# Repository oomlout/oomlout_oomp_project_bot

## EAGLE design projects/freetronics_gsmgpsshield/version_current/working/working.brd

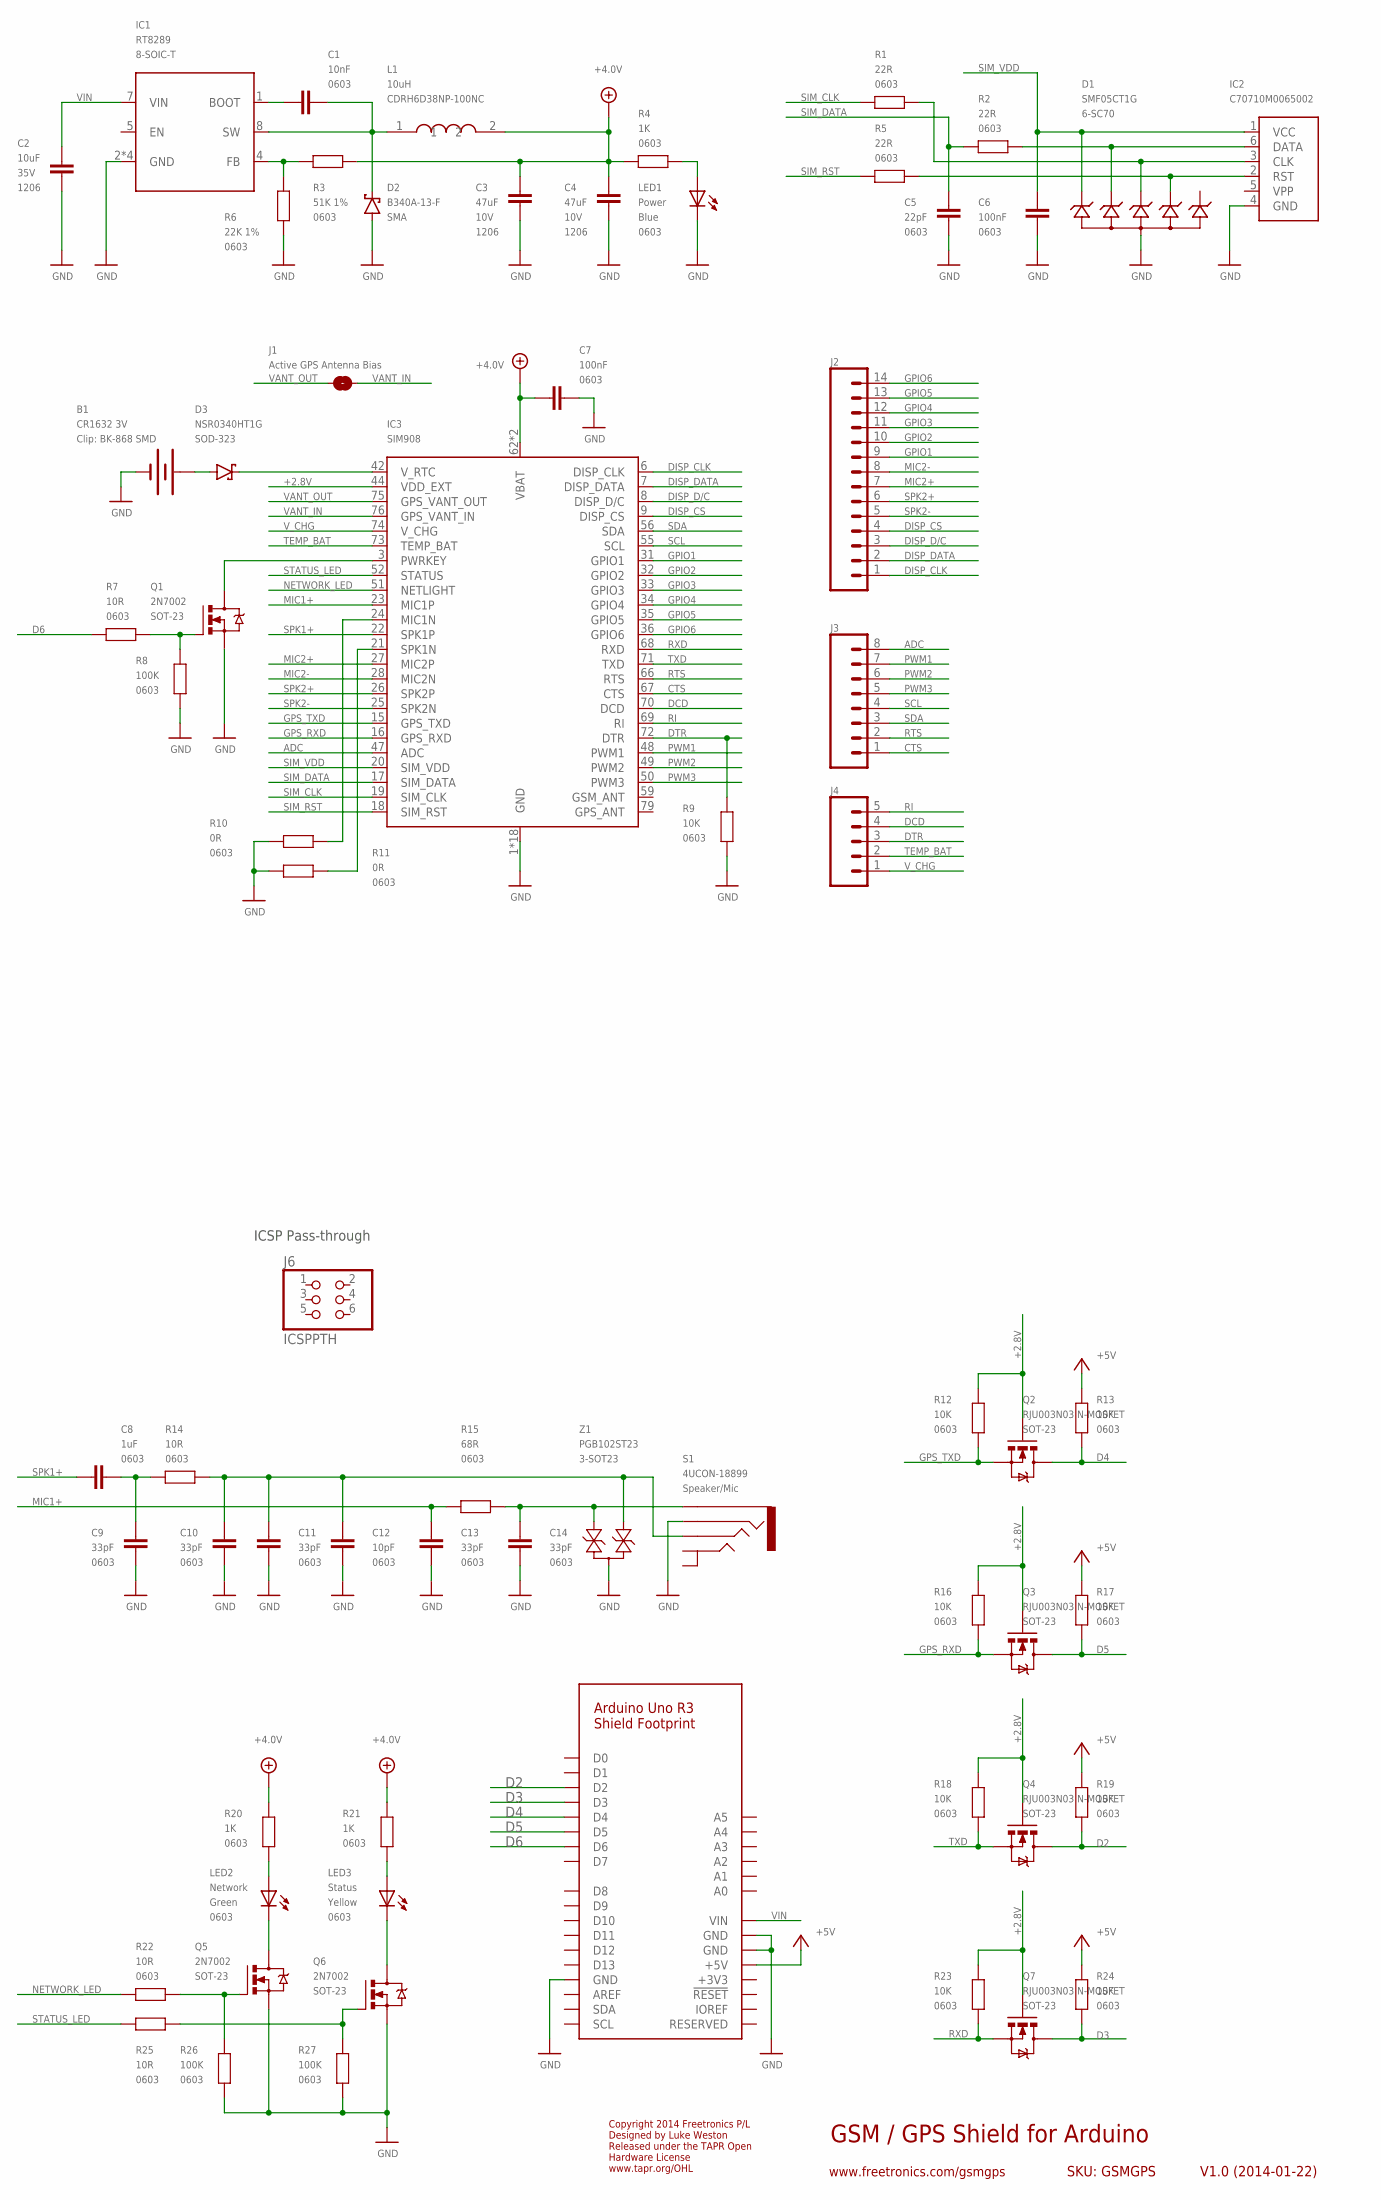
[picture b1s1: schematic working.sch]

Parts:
B1: CR1632 3V; BATCON_16MM
C1: 10nF; 0603
C2: 10uF; C1206; VOLTAGE 35V
C3, C4: 47uF; C1206; VOLTAGE 10V
C5: 22pF; 0603
C6, C7: 100nF; 0603
C8: 1uF; 0603
C9, C10, C11, C13, C14: 33pF; 0603
C12: 10pF; 0603
D1: SMF05CT1G; SC70-6
D2: B340A-13-F; SMA
D3: NSR0340HT1G; SOD-323
IC1: RT8289; SO08T
IC2: C70710M0065002
IC3: SIM908
J1: Active GPS Antenna Bias; SJ
J2: M14; 1X14
J3: M08STD; 1X08
J4: M05PTH; 1X05
J5: ARDUINO-SHIELD_R3_NOISP
J6: ICSPPTH; 2X03PTH
L1: 10uH; CDRH
LED1: Power; LED-0603
LED2: Network; LED-0603
LED3: Status; LED-0603
Q1, Q5, Q6: 2N7002; SOT23-3
Q2, Q3, Q4, Q7: RJU003N03 N-MOSFET; SOT32-3
R1, R2, R5: 22R; 0603
R3: 51K 1%; 0603
R4, R20, R21: 1K; 0603
R6: 22K 1%; 0603
R7, R14, R22, R25: 10R; 0603
R8, R26, R27: 100K; 0603
R9, R12, R13, R16, R17, R18, R19, R23, R24: 10K; 0603
R10, R11: 0R; 0603
R15: 68R; 0603
S1: 4UCON-18899
Z1: PGB102ST23; SOT23-3

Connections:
+2.8V: IC3.44 (VDD_EXT), Q2.1 (G), Q3.1 (G), Q4.1 (G), Q7.1 (G), R12.1, R16.1, R18.1, R23.1
+3V3: J5.3V3 (+3V3)
+4.0V: C3.1, C4.1, C7.2, IC3.62 (VBAT), IC3.63 (VBAT), L1.2, R3.1, R4.1, R20.1, R21.1
+5V: J5.+5V, R13.1, R17.1, R19.1, R24.1
ADC: IC3.47 (ADC), J3.8
CTS: IC3.67 (CTS), J3.1
D2: J5.D2, Q4.3 (D), R19.2
D3: J5.D3, Q7.3 (D), R24.2
D4: J5.D4, Q2.3 (D), R13.2
D5: J5.D5, Q3.3 (D), R17.2
D6: J5.D6, R7.2
DCD: IC3.70 (DCD), J4.4
DISP_CLK: IC3.6 (DISP_CLK), J2.1
DISP_CS: IC3.9 (DISP_CS), J2.4
DISP_D/C: IC3.8 (DISP_D/C), J2.3
DISP_DATA: IC3.7 (DISP_DATA), J2.2
DTR: IC3.72 (DTR), J4.3, R9.1
GND: B1.GND (-), C2.2, C3.2, C4.2, C5.1, C6.1, C7.1, C9.1, C10.1, C11.1, C12.1, C13.1, C14.1, D1.2 (A2), D2.A, IC1.2 (GND), IC1.3 (GND), IC1.6 (GND), IC1.PAD (GND), IC2.4 (GND), IC3.1 (GND), IC3.2 (GND), IC3.5 (GND), IC3.10 (GND), IC3.14 (GND), IC3.37 (GND), IC3.40 (GND), IC3.41 (GND), IC3.43 (GND), IC3.57 (GND), IC3.58 (GND), IC3.60 (GND), IC3.61 (GND), IC3.64 (GND), IC3.65 (GND), IC3.77 (GND), IC3.78 (GND), IC3.80 (GND), J5.GND, J5.GND@0 (GND), J5.GND@1 (GND), LED1.C, Q1.2 (S), Q5.2 (S), Q6.2 (S), R6.1, R8.1, R9.2, R10.2, R11.2, R26.1, R27.1, S1.4, Z1.3
GPIO1: IC3.31 (GPIO1), J2.9
GPIO2: IC3.32 (GPIO2), J2.10
GPIO3: IC3.33 (GPIO3), J2.11
GPIO4: IC3.34 (GPIO4), J2.12
GPIO5: IC3.35 (GPIO5), J2.13
GPIO6: IC3.36 (GPIO6), J2.14
GPS_RXD: IC3.16 (GPS_RXD), Q3.2 (S), R16.2
GPS_TXD: IC3.15 (GPS_TXD), Q2.2 (S), R12.2
MIC1+: C13.2, IC3.23 (MIC1P), R15.1
MIC2+: IC3.27 (MIC2P), J2.7
MIC2-: IC3.28 (MIC2N), J2.8
unnamed: LED1.A, R4.2
unnamed: LED2.C, Q5.3 (D)
unnamed: LED3.C, Q6.3 (D)
unnamed: Q5.1 (G), R22.1, R26.2
unnamed: Q6.1 (G), R25.1, R27.2
unnamed: D3.K, IC3.42 (V_RTC)
unnamed: IC3.3 (PWRKEY), Q1.3 (D)
unnamed: B1.PWR@1 (+), D3.A
unnamed: IC3.21 (SPK1N), R11.1
unnamed: IC3.24 (MIC1N), R10.1
unnamed: D1.5 (K5), IC2.2 (RST), R5.1
unnamed: D1.4 (K4), IC2.3 (CLK), R1.1
unnamed: D1.3 (K3), IC2.6 (DATA), R2.1
unnamed: C14.2, R15.2, S1.1, Z1.2
unnamed: C10.2, C11.2, C12.2, R14.2, S1.3, Z1.1
unnamed: C8.1, C9.2, R14.1
unnamed: Q1.1 (G), R7.1, R8.2
unnamed: LED3.A, R21.2
unnamed: LED2.A, R20.2
unnamed: C1.1, D2.K, IC1.8 (SW), L1.1
unnamed: IC1.4 (FB), R3.2, R6.2
unnamed: C1.2, IC1.1 (BOOT)
NETWORK_LED: IC3.51 (NETLIGHT), R22.2
PWM1: IC3.48 (PWM1), J3.7
PWM2: IC3.49 (PWM2), J3.6
PWM3: IC3.50 (PWM3), J3.5
RI: IC3.69 (RI), J4.5
RTS: IC3.66 (RTS), J3.2
RXD: IC3.68 (RXD), Q7.2 (S), R23.2
SCL: IC3.55 (SCL), J3.4
SDA: IC3.56 (SDA), J3.3
SIM_CLK: IC3.19 (SIM_CLK), R1.2
SIM_DATA: C5.2, IC3.17 (SIM_DATA), R2.2
SIM_RST: IC3.18 (SIM_RST), R5.2
SIM_VDD: C6.2, D1.1 (K1), IC2.1 (VCC), IC3.20 (SIM_VDD)
SPK1+: C8.2, IC3.22 (SPK1P)
SPK2+: IC3.26 (SPK2P), J2.6
SPK2-: IC3.25 (SPK2N), J2.5
STATUS_LED: IC3.52 (STATUS), R25.2
TEMP_BAT: IC3.73 (TEMP_BAT), J4.2
TXD: IC3.71 (TXD), Q4.2 (S), R18.2
VANT_IN: IC3.76 (GPS_VANT_IN), J1.2
VANT_OUT: IC3.75 (GPS_VANT_OUT), J1.1
VIN: C2.1, IC1.7 (VIN), J5.VIN
V_CHG: IC3.74 (V_CHG), J4.1

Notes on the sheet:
GSM / GPS Shield for Arduino
V1.0 (2014-01-22)
www.freetronics.com/gsmgps
SKU: GSMGPS
Copyright 2014 Freetronics P/L Designed by Luke Weston Released under the TAPR Open Hardware License www.tapr.org/OHL
ICSP Pass-through

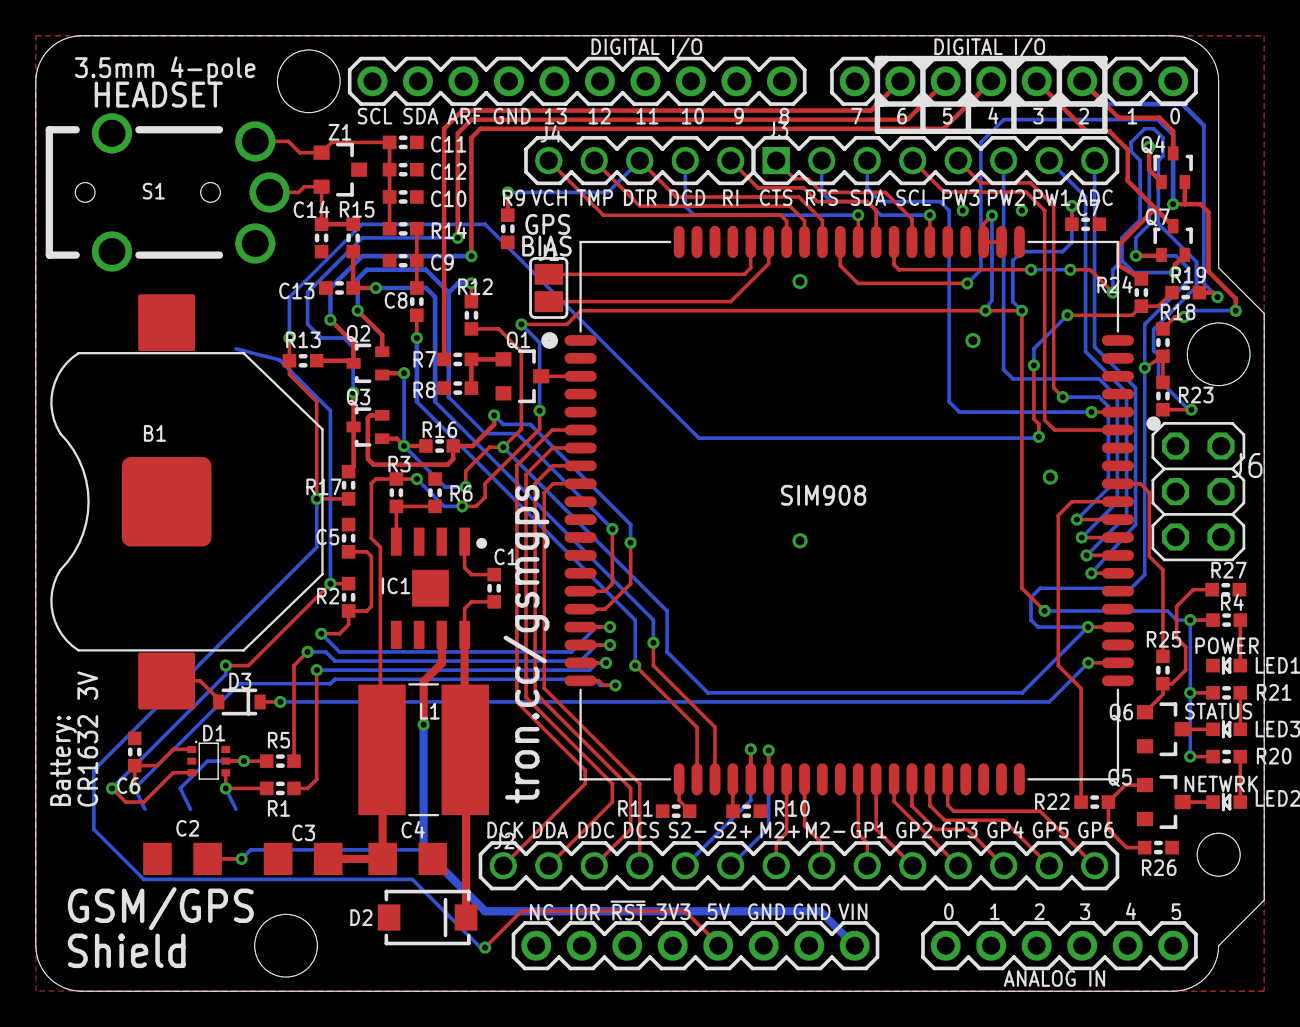
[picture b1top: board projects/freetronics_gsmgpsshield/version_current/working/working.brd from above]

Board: 2 copper layers, 68.6 x 53.3 mm, 67 parts (1 on the bottom side), 73 nets.

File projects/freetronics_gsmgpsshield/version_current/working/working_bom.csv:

"Id";"Designator";"Footprint";"Quantity";"Designation";"Supplier and ref";
1;"C14,C10,C9,C13,C11";"0603";5;"33pF";;;
2;"R1,R2,R5";"0603";3;"22R";;;
3;"R14,R25,R7,R22";"0603";4;"10R";;;
4;"C4,C3";"C1206";2;"47uF";;;
5;"Q2,Q4,Q3,Q7";"SOT32-3";4;"RJU003N03 N-MOSFET";;;
6;"C6,C7";"0603";2;"100nF";;;
7;"R15";"0603";1;"68R";;;
8;"R27,R26,R8";"0603";3;"100K";;;
9;"R20,R21,R4";"0603";3;"1K";;;
10;"Q1,Q5,Q6";"SOT23-3";3;"2N7002";;;
11;"R9,R18,R24,R19,R12,R13,R23,R16,R17";"0603";9;"10K";;;
12;"D2";"SMA";1;"B340A-13-F";;;
13;"R11,R10";"0603";2;"0R";;;
14;"C5";"0603";1;"22pF";;;
15;"R3";"0603";1;"51K 1%";;;
16;"L1";"CDRH";1;"10uH";;;
17;"LED3";"LED-0603";1;"Status";;;
18;"J3";"1X08";1;"";;;
19;"R6";"0603";1;"22K 1%";;;
20;"C8";"0603";1;"1uF";;;
21;"J1";"SJ";1;"Active GPS Antenna Bias";;;
22;"D1";"SC70-6";1;"SMF05CT1G";;;
23;"LED1";"LED-0603";1;"Power";;;
24;"IC3";"SIM908";1;"SIM908";;;
25;"J2";"1X14";1;"";;;
26;"LED2";"LED-0603";1;"Network";;;
27;"IC1";"SO08T";1;"RT8289";;;
28;"D3";"SOD-323";1;"NSR0340HT1G";;;
29;"J4";"1X05";1;"";;;
30;"B1";"BATCON_16MM";1;"CR1632 3V";;;
31;"S1";"4UCON-18899";1;"4UCON-18899";;;
32;"J6";"2X03PTH";1;"ICSPPTH";;;
33;"C12";"0603";1;"10pF";;;
34;"C2";"C1206";1;"10uF";;;
35;"Z1";"SOT23-3";1;"PGB102ST23";;;
36;"C1";"0603";1;"10nF";;;
37;"J5";"ARDUINO-SHIELD_R3_NOISP";1;"ARDUINO-SHIELD_R3_NOISP";;;
38;"IC2";"C70710M0065002";1;"C70710M0065002";;;

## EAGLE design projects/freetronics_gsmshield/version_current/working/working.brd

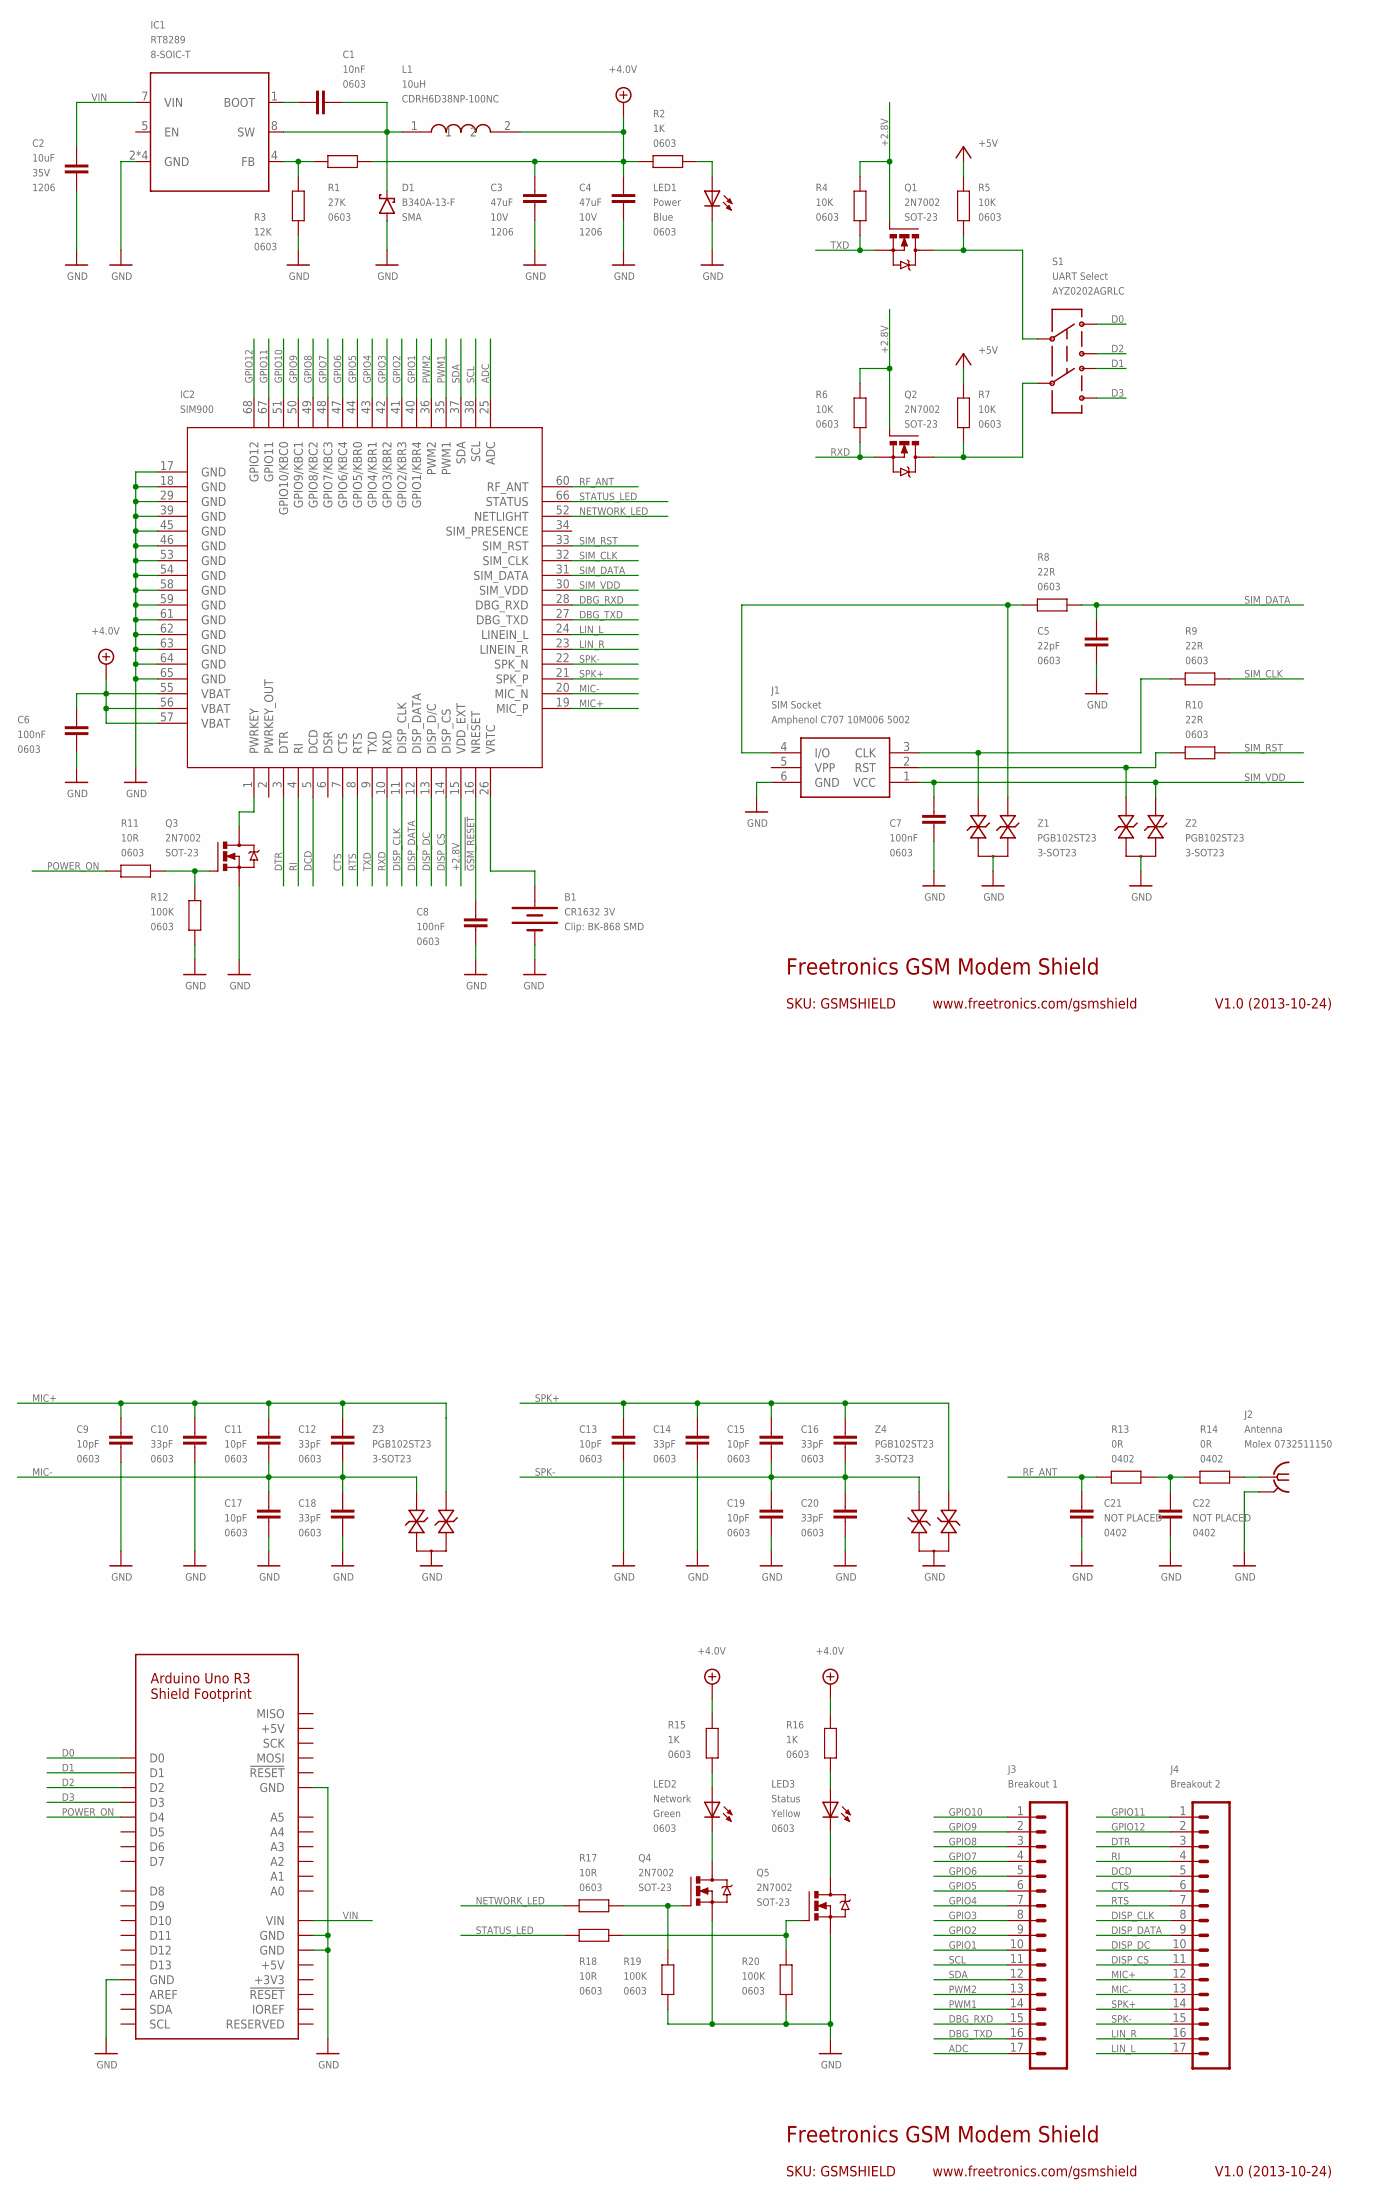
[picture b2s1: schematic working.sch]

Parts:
B1: CR1632 3V; BATCON_16MM
C1: 10nF; 0603
C2: 10uF; C1206; VOLTAGE 35V
C3, C4: 47uF; C1206; VOLTAGE 10V
C5: 22pF; 0603
C6, C7, C8: 100nF; 0603
C9, C11, C13, C15, C17, C19: 10pF; 0603
C10, C12, C14, C16, C18, C20: 33pF; 0603
C21, C22: NOT PLACED; C0402
D1: B340A-13-F; SMA
IC1: RT8289; SO08T
IC2: SIM900
J1: SIM Socket; SIMHOLDER3
J2: Antenna; J502-ND-142-0701-881/886
J3: Breakout 1; 1X17
J4: Breakout 2; 1X17
J5: ARDUINO-SHIELD_R3
L1: 10uH; CDRH
LED1: Power; LED-0603
LED2: Network; LED-0603
LED3: Status; LED-0603
Q1, Q2, Q3, Q4, Q5: 2N7002; SOT23-3
R1: 27K; 0603
R2, R15, R16: 1K; 0603
R3: 12K; 0603
R4, R5, R6, R7: 10K; 0603
R8, R9, R10: 22R; 0603
R11, R17, R18: 10R; 0603
R12, R19, R20: 100K; 0603
R13, R14: 0R; C0402
S1: UART Select; AYZ0202
Z1, Z2, Z3, Z4: PGB102ST23; SOT23-3

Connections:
!GSM_RESET: C8.2, IC2.16 (NRESET)
+2.8V: IC2.15 (VDD_EXT), Q1.1 (G), Q2.1 (G), R4.1, R6.1
+3V3: J5.3V3 (+3V3)
+4.0V: C3.1, C4.1, C6.2, IC2.55 (VBAT), IC2.56 (VBAT), IC2.57 (VBAT), L1.2, R1.1, R2.1, R15.1, R16.1
+5V: J5.+5V, R5.1, R7.1
ADC: IC2.25 (ADC), J3.17
CTS: IC2.7 (CTS), J4.6
D0: J5.D0, S1.1
D1: J5.D1, S1.4
D2: J5.D2, S1.3
D3: J5.D3, S1.6
DBG_RXD: IC2.28 (DBG_RXD), J3.15
DBG_TXD: IC2.27 (DBG_TXD), J3.16
DCD: IC2.5 (DCD), J4.5
DISP_CLK: IC2.11 (DISP_CLK), J4.8
DISP_CS: IC2.14 (DISP_CS), J4.11
DISP_DATA: IC2.12 (DISP_DATA), J4.9
DISP_DC: IC2.13 (DISP_D/C), J4.10
DTR: IC2.3 (DTR), J4.3
GND: B1.GND (-), C2.2, C3.2, C4.2, C5.1, C6.1, C7.1, C8.1, C9.1, C10.1, C13.1, C14.1, C17.1, C18.1, C19.1, C20.1, C21.1, C22.1, D1.A, IC1.2 (GND), IC1.3 (GND), IC1.6 (GND), IC1.PAD (GND), IC2.17 (GND), IC2.18 (GND), IC2.29 (GND), IC2.39 (GND), IC2.45 (GND), IC2.46 (GND), IC2.53 (GND), IC2.54 (GND), IC2.58 (GND), IC2.59 (GND), IC2.61 (GND), IC2.62 (GND), IC2.63 (GND), IC2.64 (GND), IC2.65 (GND), J1.6 (GND), J2.G@1 (GND), J2.G@2 (GND), J2.G@3 (GND), J2.G@4 (GND), J5.GND, J5.GND@0 (GND), J5.GND@1 (GND), J5.GND@2 (GND), LED1.C, Q3.2 (S), Q4.2 (S), Q5.2 (S), R3.1, R12.1, R19.1, R20.1, Z1.3, Z2.3, Z3.3, Z4.3
GPIO1: IC2.40 (GPIO1/KBR4), J3.10
GPIO2: IC2.41 (GPIO2/KBR3), J3.9
GPIO3: IC2.42 (GPIO3/KBR2), J3.8
GPIO4: IC2.43 (GPIO4/KBR1), J3.7
GPIO5: IC2.44 (GPIO5/KBR0), J3.6
GPIO6: IC2.47 (GPIO6/KBC4), J3.5
GPIO7: IC2.48 (GPIO7/KBC3), J3.4
GPIO8: IC2.49 (GPIO8/KBC2), J3.3
GPIO9: IC2.50 (GPIO9/KBC1), J3.2
GPIO10: IC2.51 (GPIO10/KBC0), J3.1
GPIO11: IC2.67 (GPIO11), J4.1
GPIO12: IC2.68 (GPIO12), J4.2
LIN_L: IC2.24 (LINEIN_L), J4.17
LIN_R: IC2.23 (LINEIN_R), J4.16
MIC+: C9.2, C10.2, C11.2, C12.2, IC2.19 (MIC_P), J4.12, Z3.2
MIC-: C11.1, C12.1, C17.2, C18.2, IC2.20 (MIC_N), J4.13, Z3.1
unnamed: LED1.A, R2.2
unnamed: LED2.C, Q4.3 (D)
unnamed: LED3.C, Q5.3 (D)
unnamed: Q4.1 (G), R17.1, R19.2
unnamed: Q5.1 (G), R18.1, R20.2
unnamed: B1.PWR@1 (+), IC2.26 (VRTC)
unnamed: J1.2 (RST), R10.2, Z2.1
unnamed: J1.3 (CLK), R9.2, Z1.1
unnamed: J1.4 (I/O), R8.2, Z1.2
unnamed: IC2.1 (PWRKEY), Q3.3 (D)
unnamed: Q3.1 (G), R11.1, R12.2
unnamed: C22.2, R13.2, R14.1
unnamed: J2.1, R14.2
unnamed: LED3.A, R16.2
unnamed: LED2.A, R15.2
unnamed: C1.1, D1.K, IC1.8 (SW), L1.1
unnamed: IC1.4 (FB), R1.2, R3.2
unnamed: C1.2, IC1.1 (BOOT)
NETWORK_LED: IC2.52 (NETLIGHT), R17.2
POWER_ON: J5.D4, R11.2
PWM1: IC2.35 (PWM1), J3.14
PWM2: IC2.36 (PWM2), J3.13
RF_ANT: C21.2, IC2.60 (RF_ANT), R13.1
RI: IC2.4 (RI), J4.4
RTS: IC2.8 (RTS), J4.7
RXD: IC2.10 (RXD), Q2.2 (S), R6.2
RXD_5V: Q2.3 (D), R7.2, S1.5
SCL: IC2.38 (SCL), J3.11
SDA: IC2.37 (SDA), J3.12
SIM_CLK: IC2.32 (SIM_CLK), R9.1
SIM_DATA: C5.2, IC2.31 (SIM_DATA), R8.1
SIM_RST: IC2.33 (SIM_RST), R10.1
SIM_VDD: C7.2, IC2.30 (SIM_VDD), J1.1 (VCC), Z2.2
SPK+: C13.2, C14.2, C15.2, C16.2, IC2.21 (SPK_P), J4.14, Z4.1
SPK-: C15.1, C16.1, C19.2, C20.2, IC2.22 (SPK_N), J4.15, Z4.2
STATUS_LED: IC2.66 (STATUS), R18.2
TXD: IC2.9 (TXD), Q1.2 (S), R4.2
TXD_5V: Q1.3 (D), R5.2, S1.2
VIN: C2.1, IC1.7 (VIN), J5.VIN

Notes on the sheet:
Freetronics GSM Modem Shield
V1.0 (2013-10-24)
www.freetronics.com/gsmshield
SKU: GSMSHIELD

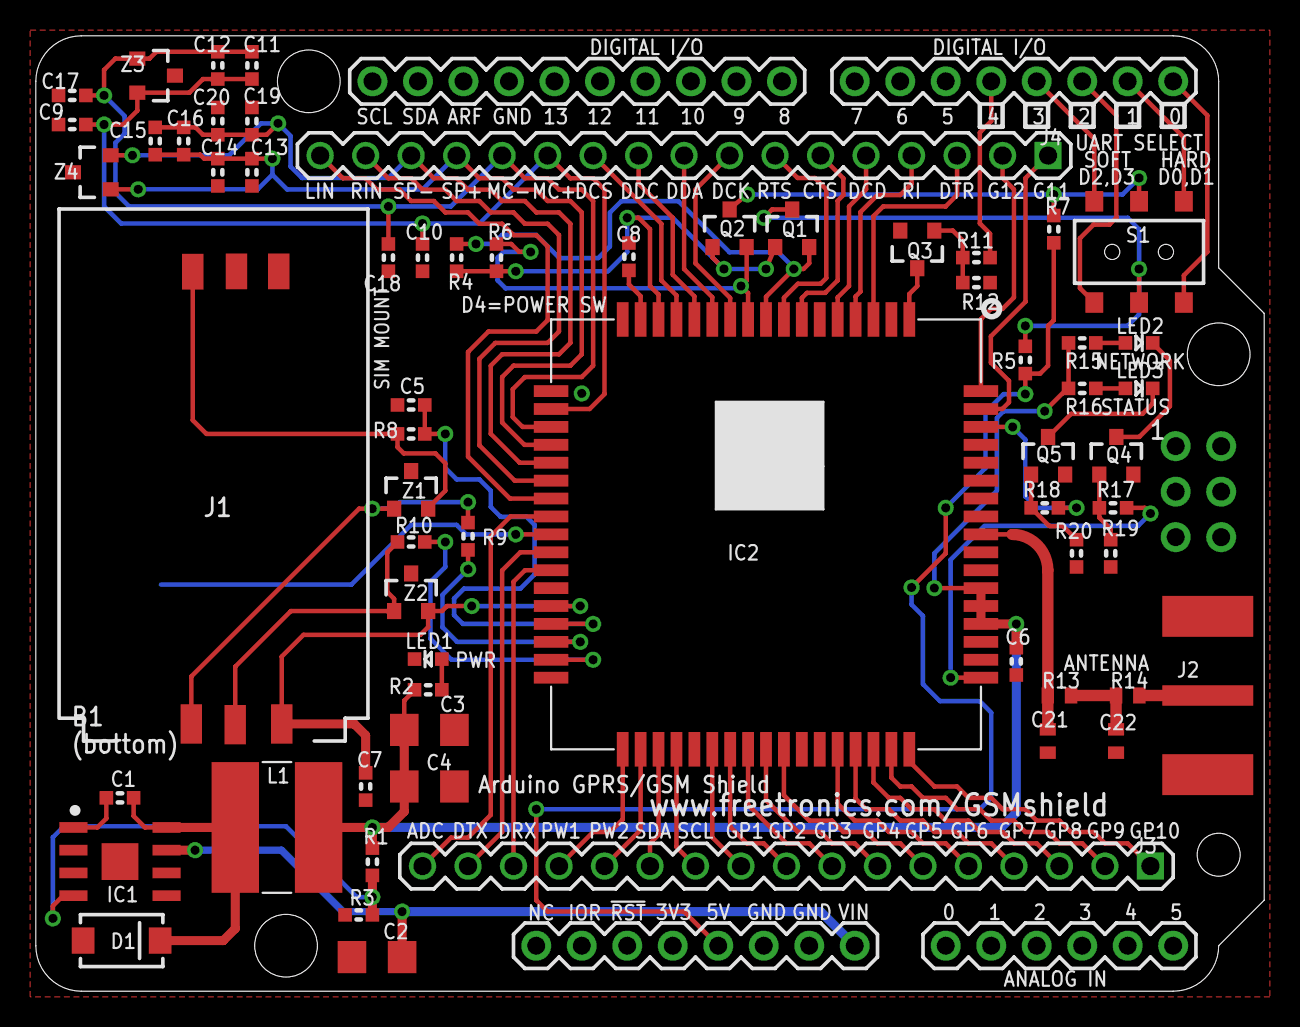
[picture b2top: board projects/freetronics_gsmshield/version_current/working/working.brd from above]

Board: 2 copper layers, 68.6 x 53.3 mm, 65 parts (1 on the bottom side), 74 nets.

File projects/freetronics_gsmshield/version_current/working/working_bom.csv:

"Id";"Designator";"Footprint";"Quantity";"Designation";"Supplier and ref";
1;"R6,R7,R5,R4";"0603";4;"10K";;;
2;"R15,R2,R16";"0603";3;"1K";;;
3;"C1";"0603";1;"10nF";;;
4;"C10,C14,C16,C18,C12,C20";"0603";6;"33pF";;;
5;"J4";"1X17";1;"Breakout 2";;;
6;"R10,R8,R9";"0603";3;"22R";;;
7;"LED2";"LED-0603";1;"Network";;;
8;"J3";"1X17";1;"Breakout 1";;;
9;"R14,R13";"C0402";2;"0R";;;
10;"S1";"AYZ0202";1;"UART Select";;;
11;"J2";"J502-ND-142-0701-881_886";1;"Antenna";;;
12;"Q1,Q5,Q2,Q4,Q3";"SOT23-3";5;"2N7002";;;
13;"C13,C17,C9,C19,C15,C11";"0603";6;"10pF";;;
14;"Z4,Z2,Z3,Z1";"SOT23-3";4;"PGB102ST23";;;
15;"R20,R19,R12";"0603";3;"100K";;;
16;"C7,C8,C6";"0603";3;"100nF";;;
17;"C22,C21";"C0402";2;"NOT PLACED";;;
18;"L1";"CDRH";1;"10uH";;;
19;"C3,C4";"C1206";2;"47uF";;;
20;"R11,R17,R18";"0603";3;"10R";;;
21;"LED3";"LED-0603";1;"Status";;;
22;"LED1";"LED-0603";1;"Power";;;
23;"IC1";"SO08T";1;"RT8289";;;
24;"C5";"0603";1;"22pF";;;
25;"C2";"C1206";1;"10uF";;;
26;"D1";"SMA";1;"B340A-13-F";;;
27;"J5";"ARDUINO-SHIELD_R3";1;"ARDUINO-SHIELD_R3";;;
28;"R3";"0603";1;"12K";;;
29;"R1";"0603";1;"27K";;;
30;"IC2";"SIM900";1;"SIM900";;;
31;"J1";"SIMHOLDER3";1;"SIM Socket";;;
32;"B1";"BATCON_16MM";1;"CR1632 3V";;;

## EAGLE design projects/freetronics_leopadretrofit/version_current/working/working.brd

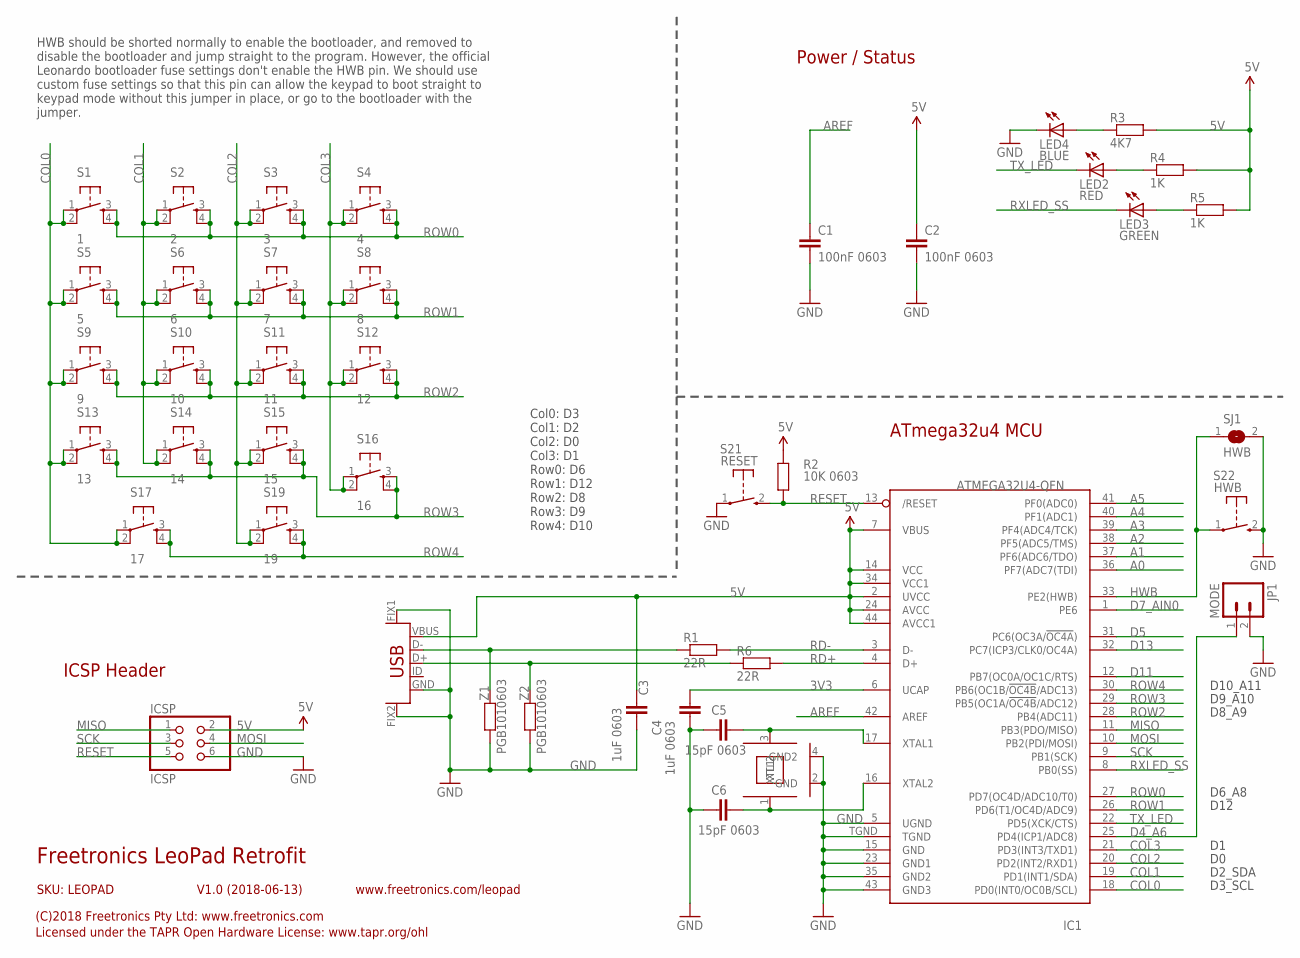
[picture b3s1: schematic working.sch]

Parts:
C1, C2: 100nF 0603; 0603
C3, C4: 1uF 0603; 0603
C5, C6: 15pF 0603; 0603
IC1: ATMEGA32U4-QFN; QFN-44N
ICSP: ICSP; 2X03
JP1: MODE; 1X02
LED2: RED; LED-0603
LED3: GREEN; LED-0603
LED4: BLUE; LED3MM
R1, R6: 22R; 0603
R2: 10K 0603; 0603
R3: 4K7; 0603
R4, R5: 1K; 0603
S1: 1; TACTILE_SWITCH_SMD
S2: 2; TACTILE_SWITCH_SMD
S3: 3; TACTILE_SWITCH_SMD
S4: 4; TACTILE_SWITCH_SMD
S5: 5; TACTILE_SWITCH_SMD
S6: 6; TACTILE_SWITCH_SMD
S7: 7; TACTILE_SWITCH_SMD
S8: 8; TACTILE_SWITCH_SMD
S9: 9; TACTILE_SWITCH_SMD
S10: 10; TACTILE_SWITCH_SMD
S11: 11; TACTILE_SWITCH_SMD
S12: 12; TACTILE_SWITCH_SMD
S13: 13; TACTILE_SWITCH_SMD
S14: 14; TACTILE_SWITCH_SMD
S15: 15; TACTILE_SWITCH_SMD
S16: 16; TACTILE_SWITCH_SMD
S17: 17; TACTILE_SWITCH_SMD
S19: 19; TACTILE_SWITCH_SMD
S21: RESET; TACTILE_SWITCH_SMD_2PIN_TINY
S22: HWB; TACTILE_SWITCH_SMD_2PIN_TINY
SJ1: HWB; SJ
U$2: USB-2P2P; USB-MICROB-MB05PMXX
XTL1: 16MHz; CRYSTAL-SMD-3X2
Z1, Z2: PGB1010603; 0603

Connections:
3V3: C4.2, IC1.6 (UCAP)
5V: C2.1, C3.1, IC1.2 (UVCC), IC1.7 (VBUS), IC1.14 (VCC), IC1.24 (AVCC), IC1.34 (VCC1), IC1.44 (AVCC1), ICSP.2, R2.2, R3.2, R4.2, R5.2, U$2.VBUS
A0: IC1.36 (PF7(ADC7(TDI))
A1: IC1.37 (PF6(ADC6/TDO))
A2: IC1.38 (PF5(ADC5/TMS))
A3: IC1.39 (PF4(ADC4/TCK))
A4: IC1.40 (PF1(ADC1))
A5: IC1.41 (PF0(ADC0))
AREF: C1.1, IC1.42 (AREF)
COL0: IC1.18 (PD0(INT0/OC0B/SCL)), S1.1, S1.2, S5.1, S5.2, S9.1, S9.2, S13.1, S13.2, S17.1, S17.2
COL1: IC1.19 (PD1(INT1/SDA)), S2.1, S2.2, S6.1, S6.2, S10.1, S10.2, S14.1, S14.2
COL2: IC1.20 (PD2(INT2/RXD1)), S3.1, S3.2, S7.1, S7.2, S11.1, S11.2, S15.1, S15.2, S19.1, S19.2
COL3: IC1.21 (PD3(INT3/TXD1)), S4.1, S4.2, S8.1, S8.2, S12.1, S12.2, S16.1, S16.2
D4_A6: IC1.25 (PD4(ICP1/ADC8)), JP1.1
D5: IC1.31 (PC6(OC3A/!OC4A!))
D7_AIN0: IC1.1 (PE6)
D11: IC1.12 (PB7(OC0A/OC1C/RTS))
D13: IC1.32 (PC7(ICP3/CLK0/OC4A))
D+: R6.1, U$2.D+, Z2.2
D-: R1.1, U$2.D-, Z1.2
GND: C1.2, C2.2, C3.2, C4.1, C5.1, C6.1, IC1.5 (UGND), IC1.15 (GND), IC1.23 (GND1), IC1.35 (GND2), IC1.43 (GND3), IC1.TGND, ICSP.6, JP1.2, LED4.K (C), S21.1, S22.2 (S), SJ1.2, U$2.FIX1 (TAB1), U$2.FIX2 (TAB2), U$2.GND, XTL1.2 (GND), XTL1.4 (GND2), Z1.1, Z2.1
HWB: IC1.33 (PE2(HWB)), S22.1, SJ1.1
MISO: IC1.11 (PB3(PDO/MISO)), ICSP.1
MOSI: IC1.10 (PB2(PDI/MOSI)), ICSP.4
unnamed: LED4.A, R3.1
unnamed: LED2.A, R4.1
unnamed: LED3.A, R5.1
unnamed: C5.2, IC1.17 (XTAL1), XTL1.3 (XTL2)
unnamed: C6.2, IC1.16 (XTAL2), XTL1.1 (XTL1)
RD+: IC1.4 (D+), R6.2
RD-: IC1.3 (D-), R1.2
RESET: IC1.13 (/RESET), ICSP.5, R2.1, S21.2 (S)
ROW0: IC1.27 (PD7(OC4D/ADC10/T0)), S1.3, S1.4, S2.3, S2.4, S3.3, S3.4, S4.3, S4.4
ROW1: IC1.26 (PD6(T1/OC4D/ADC9)), S5.3, S5.4, S6.3, S6.4, S7.3, S7.4, S8.3, S8.4
ROW2: IC1.28 (PB4(ADC11)), S9.3, S9.4, S10.3, S10.4, S11.3, S11.4, S12.3, S12.4
ROW3: IC1.29 (PB5(OC1A/!OC4B!/ADC12)), S13.3, S13.4, S14.3, S14.4, S15.3, S15.4, S16.3, S16.4
ROW4: IC1.30 (PB6(OC1B/!OC4B!/ADC13)), S17.3, S17.4, S19.3, S19.4
RXLED_SS: IC1.8 (PB0(SS)), LED3.C
SCK: IC1.9 (PB1(SCK)), ICSP.3
TX_LED: IC1.22 (PD5(XCK/CTS)), LED2.C

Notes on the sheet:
ICSP Header
ATmega32u4 MCU
HWB should be shorted normally to enable the bootloader, and removed to disable the bootloader and jump straight to the program. However, the official Leonardo bootloader fuse settings don't enable the HWB pin. We should use custom fuse settings so that this pin can allow the keypad to boot straigh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
Freetronics LeoPad Retrofit
V1.0 (2018-06-13)
SKU: LEOPAD
(C)2018 Freetronics Pty Ltd: www.freetronics.com
Licensed under the TAPR Open Hardware License: www.tapr.org/ohl
www.freetronics.com/leopad
Power / Status
D2_SDA
D3_SCL
D10_A11
D9_A10
D8_A9
D6_A8
D12
Col0: D3 Col1: D2 Col2: D0 Col3: D1 Row0: D6 Row1: D12 Row2: D8 Row3: D9 Row4: D10

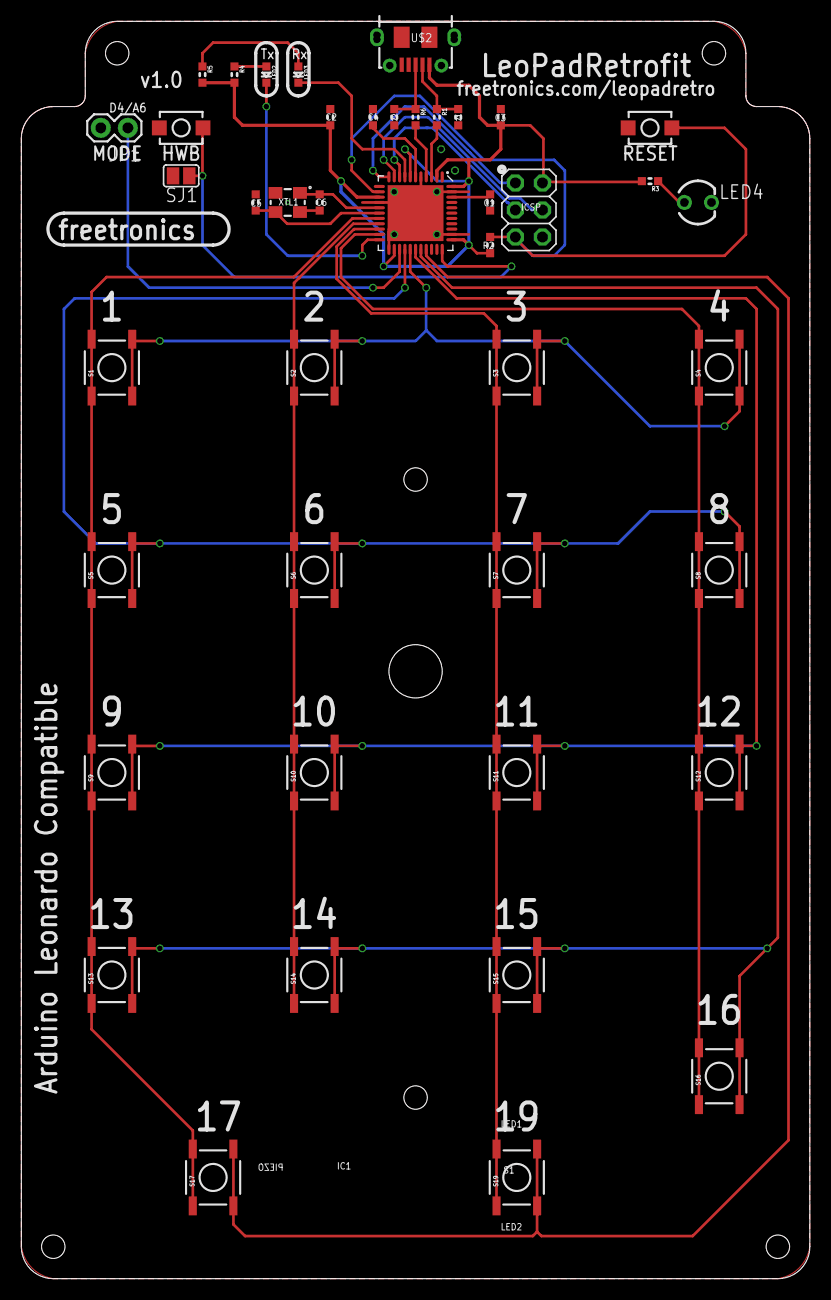
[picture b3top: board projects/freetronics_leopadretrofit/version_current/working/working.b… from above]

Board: 2 copper layers, 74.0 x 118.0 mm, 43 parts (0 on the bottom side), 30 nets.

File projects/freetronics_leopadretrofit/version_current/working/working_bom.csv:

"Id";"Designator";"Footprint";"Quantity";"Designation";"Supplier and ref";
1;"S17";"TACTILE_SWITCH_SMD";1;"17";;;
2;"@HOLE4,@HOLE3,@HOLE5,@HOLE1,@HOLE2,@HOLE0,@HOLE6";"";7;"";;;
3;"C4,C3";"0603";2;"1uF 0603";;;
4;"S21";"TACTILE_SWITCH_SMD_2PIN_TINY";1;"RESET";;;
5;"C5,C6";"0603";2;"15pF 0603";;;
6;"S12";"TACTILE_SWITCH_SMD";1;"12";;;
7;"S13";"TACTILE_SWITCH_SMD";1;"13";;;
8;"S9";"TACTILE_SWITCH_SMD";1;"9";;;
9;"C2,C1";"0603";2;"100nF 0603";;;
10;"S3";"TACTILE_SWITCH_SMD";1;"3";;;
11;"JP1";"1X02";1;"MODE";;;
12;"ICSP0";"2X03";1;"ICSP";;;
13;"S22";"TACTILE_SWITCH_SMD_2PIN_TINY";1;"HWB";;;
14;"Z1,Z2";"0603";2;"PGB1010603";;;
15;"S16";"TACTILE_SWITCH_SMD";1;"16";;;
16;"S5";"TACTILE_SWITCH_SMD";1;"5";;;
17;"LED4";"LED3MM";1;"BLUE";;;
18;"R1,R6";"0603";2;"22R";;;
19;"LED2";"LED-0603";1;"RED";;;
20;"R2";"0603";1;"10K 0603";;;
21;"SJ1";"SJ";1;"HWB";;;
22;"U$2";"USB-MICROB-MB05PMXX";1;"USB-2P2P";;;
23;"R5,R4";"0603";2;"1K";;;
24;"S2";"TACTILE_SWITCH_SMD";1;"2";;;
25;"LED3";"LED-0603";1;"GREEN";;;
26;"S8";"TACTILE_SWITCH_SMD";1;"8";;;
27;"S1";"TACTILE_SWITCH_SMD";1;"1";;;
28;"S6";"TACTILE_SWITCH_SMD";1;"6";;;
29;"S14";"TACTILE_SWITCH_SMD";1;"14";;;
30;"IC1";"QFN-44N";1;"ATMEGA32U4-QFN";;;
31;"R3";"0603";1;"4K7";;;
32;"S4";"TACTILE_SWITCH_SMD";1;"4";;;
33;"S10";"TACTILE_SWITCH_SMD";1;"10";;;
34;"XTL1";"CRYSTAL-SMD-3X2";1;"16MHz";;;
35;"S15";"TACTILE_SWITCH_SMD";1;"15";;;
36;"S11";"TACTILE_SWITCH_SMD";1;"11";;;
37;"S7";"TACTILE_SWITCH_SMD";1;"7";;;
38;"S19";"TACTILE_SWITCH_SMD";1;"19";;;

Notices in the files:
projects/freetronics_gsmgpsshield/version_current/working/working.brd:
Copyright 2014 Freetronics Pty Ltd
Released under the terms of the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
projects/freetronics_lssm/version_current/working/working.brd:
Open Hardware Licence
projects/freetronics_pbase170/version_current/working/working.brd:
TAPR Open Hardware License tapr.org/OHL
Copyright 2015 Freetronics Pty Ltd
parts and their libraries:
freetronics-original: Licensing: CC v3.0 Share-Alike You are welcome to use this library for commercial purposes.
